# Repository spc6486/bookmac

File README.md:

# BookMac Replicas

Functional replicas of the BookMac and BookMac Mini, the 1985 tablet concepts Hartmut Esslinger (frog design) created for Apple. Esslinger's own *Keep It Simple* calls them the MacBook and MacBook Mini. Each unit is built around a Raspberry Pi 5 with a 9.7" 2048×1536 touchscreen, an internal mechanical keyboard, a battery-backed power system and period-style rear ports. Their main use is classic Mac OS (7.5.5) under SheepShaver, but they are general-purpose Pi 5 computers and run other operating systems and emulators, including Basilisk II.

There are two units, one per concept: the full-size **BookMac** and the smaller **BookMac Mini**. They share most of the hardware and all of the software; the differences are listed in `docs/` and `decals/README.md`.

The full-size concept has a floppy drive slot. This build closes it with a printed cover (`enclosure/bookmac/floppy-slot-cover.stl`), because the space behind it holds the batteries, rear ports and speakers. The Mini concept shows no floppy provision.

Both concepts are documented in Paul Kunkel, *AppleDesign* (Graphis, 1997), and Hartmut Esslinger, *Keep It Simple* (Arnoldsche, 2013). The build was inspired by Kevin Noki's functional replicas.

> **Work in progress.** This repository documents a personal build as it evolves. Expect inaccuracies, undocumented changes, and parts of the documentation that lag behind the hardware. Verify dimensions, pinouts and part numbers against your own parts before building, and please open an issue when you find an error.

> **Hobbyist designs, reference only.** The PCBs, wiring and enclosure were designed by a hobbyist, not a professional electrical or mechanical engineer. They have not been independently reviewed for electrical safety, battery safety, thermal performance or regulatory compliance. Use them as a reference for your own work, at your own risk. This is especially important for anything involving the lithium battery packs or the UPS.

> **Not affiliated with, sponsored by, or endorsed by Apple Inc.** Apple and Macintosh are trademarks of Apple Inc., used here only to identify the original concept this replica is based on. This repository contains no Apple logos or artwork.

---

## Repository contents

| Folder | Contents |
|---|---|
| `pcb/keyboard/` | 58-key matrix PCB (Cherry MX Low Profile footprint, 5 × 14): `.sch`, `.brd`, BOM, CPL |
| `pcb/keyboard-controller/` | ATmega32U4 USB-C keyboard controller: `.sch`, `.brd`, BOM, CPL |
| `pcb/rear-port-adb/` | ATmega32U4 ADB-to-USB converter (TMK) with Mini-DIN 4: `.sch`, `.brd`, BOM, CPL |
| `pcb/rear-port-power/` | Rear power and reset switch board: `.sch`, `.brd`, BOM, CPL |
| `pcb/rear-port-av/` | Composite RCA, 3.5 mm headphone pass-through, Mini-DIN 8: `.brd`, BOM, CPL |
| `firmware/keyboard/` | QMK keyboard definition, keymap and pre-built image for the internal keyboard |
| `firmware/adb/` | Pre-built TMK `adb_usb` unimap image for the ADB converter, with a link to the source |
| `enclosure/bookmac/` | Full-size STEP model and STLs, one file per part |
| `enclosure/bookmac-mini/` | Mini STEP model and STLs, one file per part |
| `enclosure/jigs/` | Keycap holder and keycap decal holder |
| `decals/` | Keycap legend decals for both units, 1:1 exports of the original artwork (SVG with outlined text, and PDF), and a README listing the differences |
| `docs/` | Components list and wiring, Pi 5 pinout, PiPower 5 installation, reference photos (`docs/images/`) |

Board files are EAGLE 9.7 format, exported from Autodesk Fusion Electronics.

Gerber packages for each board revision are attached to the GitHub Releases rather than committed.

## Related software

The Pi-side software lives in separate repositories:

| Repository | Purpose |
|---|---|
| [emulator-manager](https://github.com/spc6486/emulator-manager) | Tray launcher for SheepShaver / Basilisk II; touch shim, display geometry |
| [battery-monitor](https://github.com/spc6486/battery-monitor) | PiPower 5 (I2C) battery monitoring and safe shutdown |
| [emu-serial-bridge](https://github.com/spc6486/emu-serial-bridge) | Serial bridge between the emulated Mac and Pi-side handlers (battery, brightness, volume) |
| [emu-control-strip](https://github.com/spc6486/emu-control-strip) | Native Mac OS 7.5 Control Strip modules, Brightness control panel, Power Manager extension |
| [emu-homecontrol](https://github.com/spc6486/emu-homecontrol) | Classic Mac OS Home Assistant client |
| [brightness-control](https://github.com/spc6486/brightness-control) | Backlight brightness via Pi 5 hardware PWM |
| [volume-control](https://github.com/spc6486/volume-control) | Volume, mute and GPIO headphone/speaker toggle |
| [display-calibrator](https://github.com/spc6486/display-calibrator) | Display borders and touchscreen calibration for custom bezels |
| [kiosk-manager](https://github.com/spc6486/kiosk-manager) | Kiosk mode, boot splash and startup sound |

## Hardware overview

| Area | Parts |
|---|---|
| Compute | Raspberry Pi 5 |
| Display | 9.7" iPad Retina LCD, LTL097QL01-A01 (2048 × 1536), in both units. Full-size: VSDISPLAY VS-RTD2556HC-V2 controller. Mini: PCB800869. Each controller comes with a TLT-iPAD3 eDP adapter. |
| Touch | SingWon capacitive overlay, USB |
| Backlight | Controller's PWM output separated from the backlight DIM line, which is then driven from Pi GPIO12 (hardware PWM). See [display controller modifications](docs/components-and-wiring.md#4-display-controller-modifications). |
| Audio | Display controller's amplifier and speakers; GPIO24 switches speaker / headphones through the jack-detect line (same section) |
| Power | SunFounder PiPower 5 UPS, two 3.7 V LiPo packs in 2S, 12 V barrel input. Observed runtime is about 3–6 h. |
| Keyboard | Custom 58-key PCB, Cherry MX Low Profile switches, Gateron low-profile plate-mount stabilizers, QMK controller |
| Rear ports | 12 V DC, ADB, headphone, composite (RCA), Mini-DIN 8 |

A full components list with wiring is in `docs/`.

## Photos and reference images

<table>
<tr><td width="50%" valign="top"><br><sub>Finished BookMac Mini</sub></td><td width="50%" valign="top"><br><sub>Painted full-size case</sub></td></tr>
<tr><td width="50%" valign="top"><br><sub>Rendering of the full-size internal layout</sub></td><td width="50%" valign="top"><br><sub>Full-size internal layout, current wiring</sub></td></tr>
<tr><td width="50%" valign="top"><br><sub>Back of the full-size screen assembly: panel, speakers, display wiring</sub></td><td width="50%" valign="top"><br><sub>BookMac Mini internal layout</sub></td></tr>
<tr><td width="50%" valign="top"><br><sub>Rendering of the BookMac Mini</sub></td><td width="50%" valign="top"><br><sub>Rendering of the BookMac Mini internal layout</sub></td></tr>
</table>

The photos show the finished replica, including the Apple-style markings that are part of the concept's appearance. They are for reference; the repository does not distribute logo artwork.

## Finishing

These are the materials used on the original enclosures. Treat them as one working example, not a requirement:

- Both units printed in ASA
- Bondo glazing putty for layer lines and small defects
- SprayMAX 1K Plastic Adhesion Promoter (article 3680009)
- SprayMAX 1K white high-build primer (article 3680403), sanded after priming
- SprayMAX 1K FillClean base coat, custom-mix can (article 3682071), filled to a RAL color:
  - **BookMac (full size):** RAL 7044, as a Platinum gray match
  - **BookMac Mini:** RAL 1013, as a Snow White match

  RAL 1013 on both units would be the period-correct choice for the 1985 concepts.
- SprayMAX 2K clear coat, satin (article 3680067)
- Experts Choice decals, item 123 (artwork in `decals/`)
- Microscale MicroSet and MicroSol to help the decals conform to the concave keycaps

General practice and precautions:

- **Read the technical and safety data sheets** for every product, and follow their flash times, recoat windows and temperature and humidity ranges. They differ between products and brands.
- **2K clears typically contain isocyanates.** Use a properly fitted respirator rated for the product per its SDS, gloves and eye protection, and good ventilation. Keep other people and pets away from the spray area.
- **Work in thin coats.** Fill layer lines with thin passes of putty, then use high-build primer to bring the surface level. Sand the primer progressively finer before the base coat. Heavy single coats sag and trap solvent.
- **Test on scrap first.** That includes adhesion promoter on your filament, solvent compatibility of primer and paint with the printed part, and clear coat over a sample decal. Some solvent clears attack decals unless the first coats are light mists.
- **Decal setting solutions** soften the decal film. Apply sparingly and let them work before touching the decal; check the manufacturer's instructions for order of use.
- **Keep mating surfaces thin.** Avoid building up primer and paint on surfaces where parts join, such as bezel seats, lips and screw bosses. Excess film thickness makes parts fit poorly. Mask them, or keep coats there light.
- **Allow full cure** before assembly and handling. Fasteners and heat-set inserts can mar paint that has not fully cured.

## Building

Start with [`docs/components-and-wiring.md`](docs/components-and-wiring.md). In particular:

- **Rear power switch:** fit the momentary ALPS SPPJ223200 in place of the latching SPPJ222200 shown in the schematic. The PiPower 5 needs a momentary button.
- **Battery packs:** balance the two packs to within 50 mV of each other before wiring them in series.
- **Display controller:** backlight dimming and speaker/headphone switching need two modifications to the display controller, and both can damage it if done carelessly. Locate and test each point before soldering.
- **Keyboard ribbon:** pins 1–20 must match end to end, from the keyboard PCB's solder holes to the controller's IDC header. Check with a meter before powering up.

Fasteners are M3 and M2 pan-head screws into knurled heat-set inserts, plus M2.5 brass standoffs for the PiPower 5. The Pi 5 stacks on top of the PiPower 5.

The keyboard firmware is built with QMK; see `firmware/keyboard/README.md`. The ADB converter uses TMK's [`converter/adb_usb`](https://github.com/tmk/tmk_keyboard/tree/master/converter/adb_usb).

## Licenses

| Part | License |
|---|---|
| Enclosure (STEP/STL), PCB design files, BOMs, decals, documentation | [CC BY-NC-SA 4.0](https://creativecommons.org/licenses/by-nc-sa/4.0/) (`LICENSE`), with the additional permission below |
| Keyboard firmware (QMK) and ADB firmware (TMK) | GPL-2.0-or-later, as inherited from QMK and TMK (`firmware/LICENSE`) |
| Pi-side software (linked repositories) | MIT, except emu-control-strip (see that repository) |

The hardware is shared for others to build, modify and enjoy, not for commercial use. ShareAlike means that if you publish a modified version, it must use the same license, so improvements stay available to everyone. Because of the non-commercial term this is not "open source hardware" in the OSHWA sense.

**Additional permission: making parts at cost.** In addition to CC BY-NC-SA 4.0, you may make and supply parts, boards or kits from this repository's hardware files **at cost**. "At cost" means the price covers only materials, fabrication, shipping and payment-processing fees: no profit and no charge for labour. Group buys on these terms are allowed. Selling for profit, charging for labour, or listing on marketplaces such as Etsy or eBay requires written permission from the maintainer (GitHub user spc6486); please open an issue to ask.

Contributions are welcome. See [CONTRIBUTING.md](CONTRIBUTING.md) for the terms that apply to them.

Both enclosures are also on Thingiverse: full-size BookMac [thing:7426168](https://www.thingiverse.com/thing:7426168), BookMac Mini [thing:7427053](https://www.thingiverse.com/thing:7427053).

## Not included

- Mac OS system software or Macintosh ROM images. Obtain these yourself.
- Apple logo artwork, the case label, or other Apple decal artwork. (Photos and renders show the finished replica with its markings; no logo artwork files are included.)

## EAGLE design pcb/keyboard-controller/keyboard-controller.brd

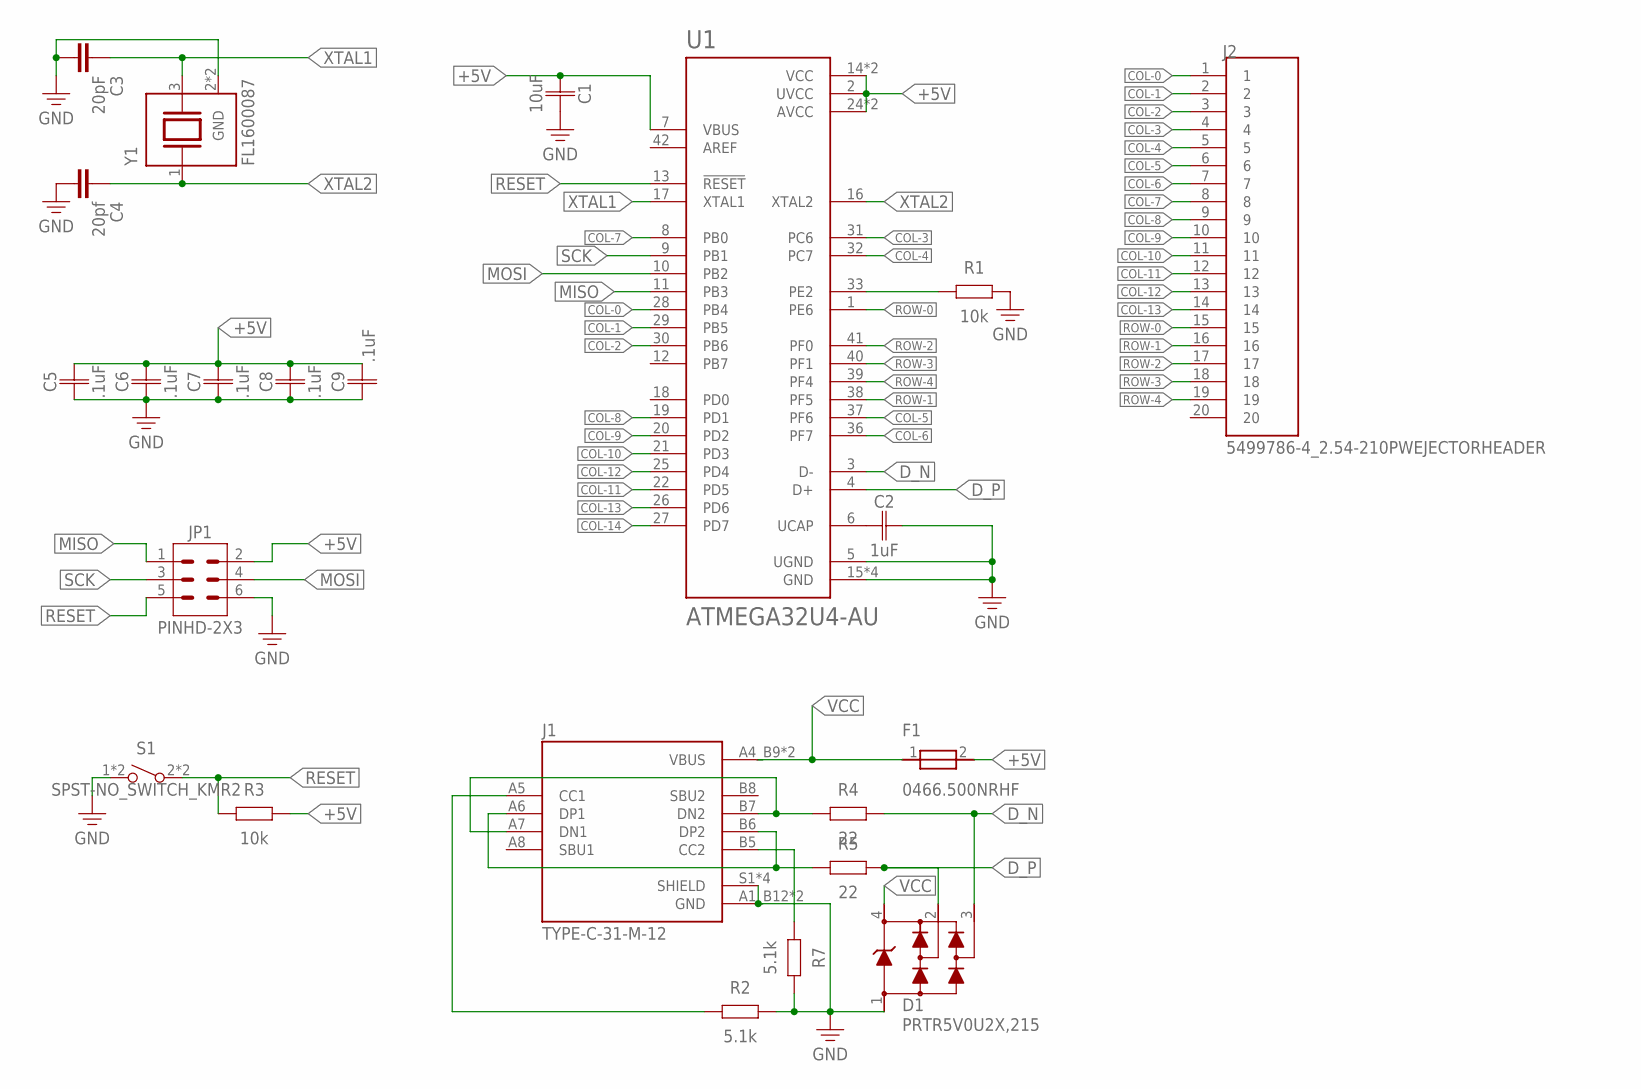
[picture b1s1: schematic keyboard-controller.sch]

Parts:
C1: 10uF; CAPC1005X60
C2: 1uF; CAPC1005X60
C3: 20pF; CAPC1005X60
C4: 20pf; CAPC1005X60
C5, C6, C7, C8, C9: .1uF; CAPC1005X60
D1: PRTR5V0U2X,215; SOT143B
F1: 0466.500NRHF; FUSC3115X66N
J1: TYPE-C-31-M-12; HRO_TYPE-C-31-M-12
J2: 5499786-4_2.54-210PWEJECTORHEADER; TE_5499786-4
JP1: PINHD-2X3; 2X03
R1, R3: 10k; RESC1005X40
R2, R7: 5.1k; RESC1005X40
R4, R5: 22; RESC1005X40
S1: SPST-NO_SWITCH_KMR2; KMR2
U1: ATMEGA32U4-AU; QFP80P1200X1200X120-44N
Y1: FL1600087; XTAL_FL1600087

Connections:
+5V: C1.1, C5.2, C6.2, C7.2, C8.2, C9.2, F1.2, JP1.2, R3.2, U1.2 (UVCC), U1.7 (VBUS), U1.14 (VCC), U1.24 (AVCC), U1.34 (VCC), U1.44 (AVCC)
CC1: J1.A5 (CC1), R2.1
CC2: J1.B5 (CC2), R7.1
COL-0: J2.1, U1.28 (PB4)
COL-1: J2.2, U1.29 (PB5)
COL-2: J2.3, U1.30 (PB6)
COL-3: J2.4, U1.31 (PC6)
COL-4: J2.5, U1.32 (PC7)
COL-5: J2.6, U1.37 (PF6)
COL-6: J2.7, U1.36 (PF7)
COL-7: J2.8, U1.8 (PB0)
COL-8: J2.9, U1.19 (PD1)
COL-9: J2.10, U1.20 (PD2)
COL-10: J2.11, U1.21 (PD3)
COL-11: J2.12, U1.22 (PD5)
COL-12: J2.13, U1.25 (PD4)
COL-13: J2.14, U1.26 (PD6)
COL-14: U1.27 (PD7)
D_N: D1.3, R4.2, U1.3 (D-)
D_P: D1.2, R5.2, U1.4 (D+)
GND: C1.2, C2.2, C3.2, C4.2, C5.1, C6.1, C7.1, C8.1, C9.1, D1.1, J1.A1_B12 (GND), J1.B1_A12 (GND), J1.S1 (SHIELD), J1.S2 (SHIELD), J1.S3 (SHIELD), J1.S4 (SHIELD), JP1.6, R1.2, R2.2, R7.2, S1.1, S1.4 (1), U1.5 (UGND), U1.15 (GND), U1.23 (GND), U1.35 (GND), U1.43 (GND), Y1.2 (GND), Y1.4 (GND)
MISO: JP1.1, U1.11 (PB3)
MOSI: JP1.4, U1.10 (PB2)
unnamed: R1.1, U1.33 (PE2)
unnamed: C2.1, U1.6 (UCAP)
unnamed: J1.A6 (DP1), J1.B6 (DP2), R5.1
unnamed: J1.A7 (DN1), J1.B7 (DN2), R4.1
RESET: JP1.5, R3.1, S1.2, S1.3 (2), U1.13 (!RESET)
ROW-0: J2.15, U1.1 (PE6)
ROW-1: J2.16, U1.38 (PF5)
ROW-2: J2.17, U1.41 (PF0)
ROW-3: J2.18, U1.40 (PF1)
ROW-4: J2.19, U1.39 (PF4)
SCK: JP1.3, U1.9 (PB1)
VCC: D1.4, F1.1, J1.A4_B9 (VBUS), J1.B4_A9 (VBUS)
XTAL1: C3.1, U1.17 (XTAL1), Y1.3 (2)
XTAL2: C4.1, U1.16 (XTAL2), Y1.1

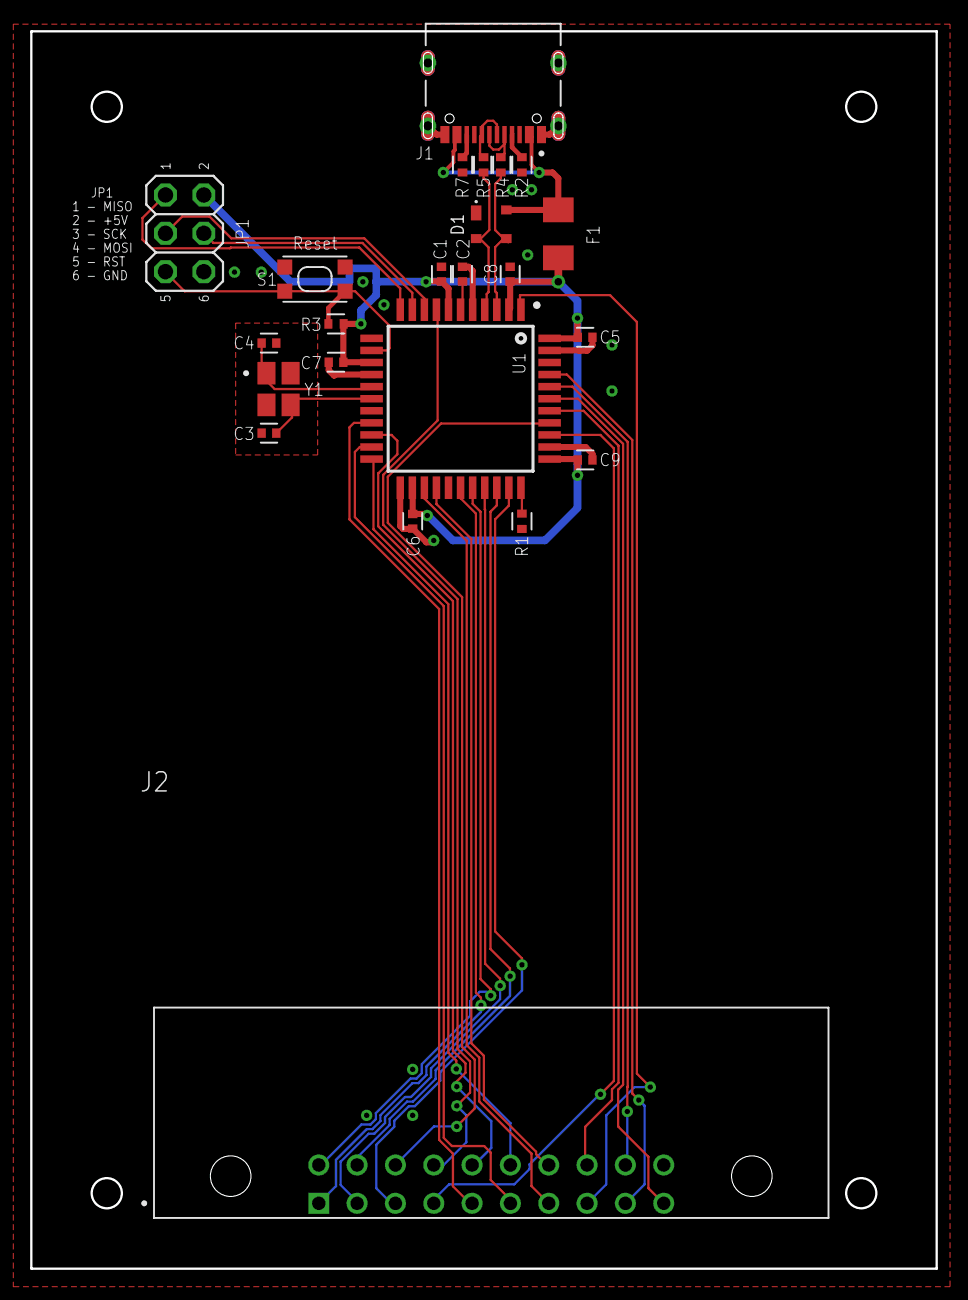
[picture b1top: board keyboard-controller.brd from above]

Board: 2 copper layers, 60.0 x 82.0 mm, 23 parts (0 on the bottom side), 36 nets.

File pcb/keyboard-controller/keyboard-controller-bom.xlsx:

Comment | Designator | Footprint | JLCPCB Part #（optional）
.1uF | C5, C6, C7, C8, C9 | CAPC1005X60
0466.500NRHF | F1 | FUSC3115X66N
10k | R1, R3 | RESC1005X40
10uF | C1 | CAPC1005X60
1uF | C2 | CAPC1005X60
20pF | C3 | CAPC1005X60
20pf | C4 | CAPC1005X60
22 | R4, R5 | RESC1005X40
5.1k | R2, R7 | RESC1005X40
5499786-4_2.54-210PWEJECTORHEADER | J2 | ORHEADER TE_5499786-4
ATMEGA32U4-AU | U1 | QFP80P1200X1200X120-44N
FL1600087 | Y1 | XTAL_FL1600087
PINHD-2X3 | JP1 | 2X03
PRTR5V0U2X,215 | D1 | SOT143B
SPST-NO_SWITCH_KMR2 | S1 | KMR2
TYPE-C-31-M-12 | J1 | HRO_TYPE-C-31-M-12

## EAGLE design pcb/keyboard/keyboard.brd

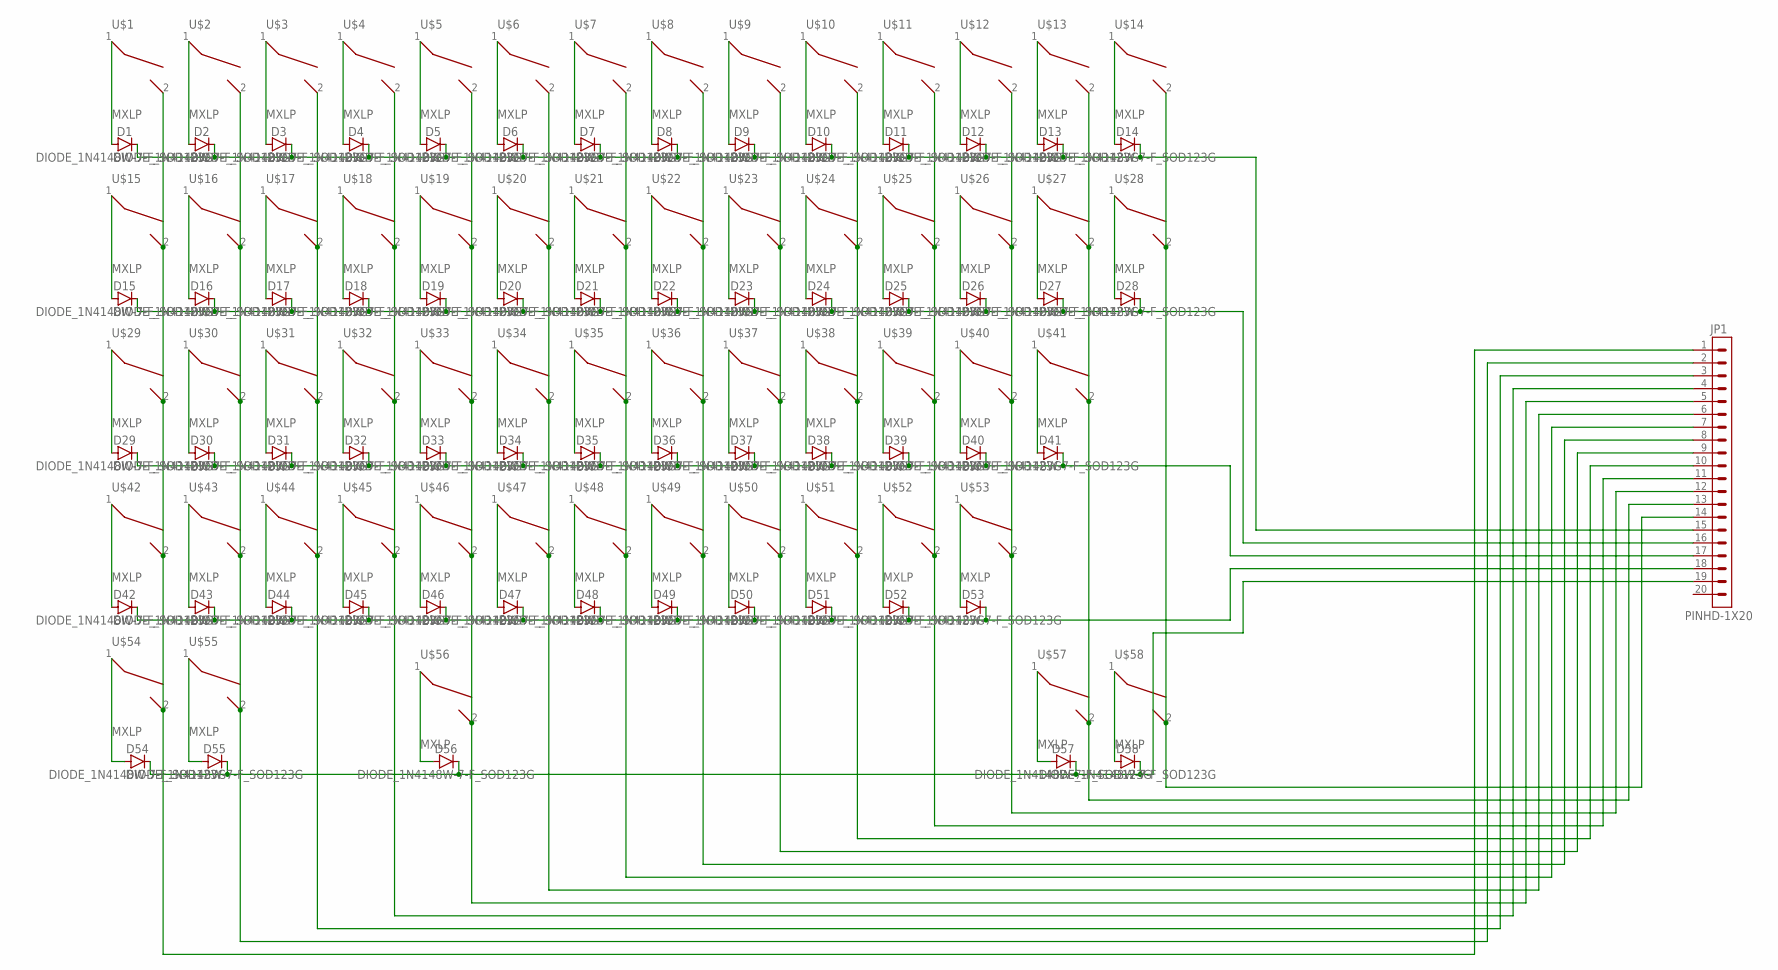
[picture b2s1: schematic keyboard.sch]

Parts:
D1, D2, D3, D4, D5, D6, D7, D8, D9, D10, D11, D12, D13, D14, D15, D16, D17, D18, D19, D20, D21, D22, D23, D24, D25, D26, D27, D28, D29, D30, D31, D32, D33, D34, D35, D36, D37, D38, D39, D40, D41, D42, D43, D44, D45, D46, D47, D48, D49, D50, D51, D52, D53, D54, D55, D56, D57, D58: DIODE_1N4148W-7-F_SOD123G; SOD3715X135
JP1: PINHD-1X20; 1X20
U$1, U$2, U$3, U$4, U$5, U$6, U$7, U$8, U$9, U$10, U$11, U$12, U$13, U$14, U$15, U$16, U$17, U$18, U$19, U$20, U$21, U$22, U$23, U$24, U$25, U$26, U$27, U$28, U$29, U$30, U$31, U$32, U$33, U$34, U$35, U$36, U$37, U$38, U$39, U$40, U$41, U$42, U$43, U$44, U$45, U$46, U$47, U$48, U$49, U$50, U$51, U$52, U$53, U$54, U$55, U$56, U$57, U$58: MXLP; CHERRY-MX-LOW-PROFILE

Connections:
unnamed: D1.2 (A), U$1.1
unnamed: D2.2 (A), U$2.1
unnamed: JP1.3, U$3.2, U$17.2, U$31.2, U$44.2
unnamed: D3.2 (A), U$3.1
unnamed: D4.2 (A), U$4.1
unnamed: D5.2 (A), U$5.1
unnamed: D6.2 (A), U$6.1
unnamed: D7.2 (A), U$7.1
unnamed: D8.2 (A), U$8.1
unnamed: D9.2 (A), U$9.1
unnamed: D10.2 (A), U$10.1
unnamed: D11.2 (A), U$11.1
unnamed: D12.2 (A), U$12.1
unnamed: D13.2 (A), U$13.1
unnamed: D14.2 (A), U$14.1
unnamed: D15.2 (A), U$15.1
unnamed: D16.2 (A), U$16.1
unnamed: D17.2 (A), U$17.1
unnamed: D18.2 (A), U$18.1
unnamed: D19.2 (A), U$19.1
unnamed: D20.2 (A), U$20.1
unnamed: D21.2 (A), U$21.1
unnamed: D22.2 (A), U$22.1
unnamed: D23.2 (A), U$23.1
unnamed: D24.2 (A), U$24.1
unnamed: D25.2 (A), U$25.1
unnamed: D26.2 (A), U$26.1
unnamed: D27.2 (A), U$27.1
unnamed: D28.2 (A), U$28.1
unnamed: D15.1 (C), D16.1 (C), D17.1 (C), D18.1 (C), D19.1 (C), D20.1 (C), D21.1 (C), D22.1 (C), D23.1 (C), D24.1 (C), D25.1 (C), D26.1 (C), D27.1 (C), D28.1 (C), JP1.16
unnamed: D29.2 (A), U$29.1
unnamed: D30.2 (A), U$30.1
unnamed: D31.2 (A), U$31.1
unnamed: D32.2 (A), U$32.1
unnamed: D33.2 (A), U$33.1
unnamed: D34.2 (A), U$34.1
unnamed: D35.2 (A), U$35.1
unnamed: D36.2 (A), U$36.1
unnamed: D37.2 (A), U$37.1
unnamed: D38.2 (A), U$38.1
unnamed: D39.2 (A), U$39.1
unnamed: D40.2 (A), U$40.1
unnamed: D41.2 (A), U$41.1
unnamed: D29.1 (C), D30.1 (C), D31.1 (C), D32.1 (C), D33.1 (C), D34.1 (C), D35.1 (C), D36.1 (C), D37.1 (C), D38.1 (C), D39.1 (C), D40.1 (C), D41.1 (C), JP1.17
unnamed: D42.2 (A), U$42.1
unnamed: D43.2 (A), U$43.1
unnamed: D44.2 (A), U$44.1
unnamed: D45.2 (A), U$45.1
unnamed: D46.2 (A), U$46.1
unnamed: D47.2 (A), U$47.1
unnamed: D48.2 (A), U$48.1
unnamed: D49.2 (A), U$49.1
unnamed: D50.2 (A), U$50.1
unnamed: D51.2 (A), U$51.1
unnamed: D52.2 (A), U$52.1
unnamed: D53.2 (A), U$53.1
unnamed: D42.1 (C), D43.1 (C), D44.1 (C), D45.1 (C), D46.1 (C), D47.1 (C), D48.1 (C), D49.1 (C), D50.1 (C), D51.1 (C), D52.1 (C), D53.1 (C), JP1.18
unnamed: D54.2 (A), U$54.1
unnamed: D55.2 (A), U$55.1
unnamed: D56.2 (A), U$56.1
unnamed: D57.2 (A), U$57.1
unnamed: D58.2 (A), U$58.1
unnamed: D54.1 (C), D55.1 (C), D56.1 (C), D57.1 (C), D58.1 (C), JP1.19
unnamed: JP1.1, U$1.2, U$15.2, U$29.2, U$42.2, U$54.2
unnamed: JP1.2, U$2.2, U$16.2, U$30.2, U$43.2, U$55.2
unnamed: JP1.4, U$4.2, U$18.2, U$32.2, U$45.2
unnamed: JP1.5, U$5.2, U$19.2, U$33.2, U$46.2, U$56.2
unnamed: JP1.6, U$6.2, U$20.2, U$34.2, U$47.2
unnamed: JP1.7, U$7.2, U$21.2, U$35.2, U$48.2
unnamed: JP1.8, U$8.2, U$22.2, U$36.2, U$49.2
unnamed: JP1.9, U$9.2, U$23.2, U$37.2, U$50.2
unnamed: JP1.10, U$10.2, U$24.2, U$38.2, U$51.2
unnamed: JP1.11, U$11.2, U$25.2, U$39.2, U$52.2
unnamed: JP1.12, U$12.2, U$26.2, U$40.2, U$53.2
unnamed: JP1.13, U$13.2, U$27.2, U$41.2, U$57.2
unnamed: JP1.14, U$14.2, U$28.2, U$58.2
ROW1: D1.1 (C), D2.1 (C), D3.1 (C), D4.1 (C), D5.1 (C), D6.1 (C), D7.1 (C), D8.1 (C), D9.1 (C), D10.1 (C), D11.1 (C), D12.1 (C), D13.1 (C), D14.1 (C), JP1.15

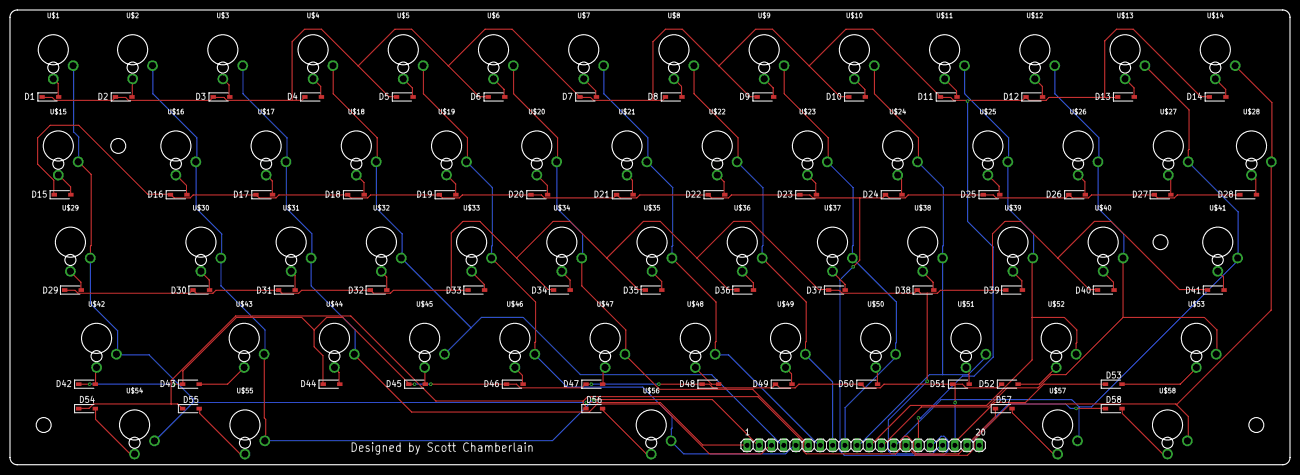
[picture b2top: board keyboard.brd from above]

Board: 2 copper layers, 266.0 x 94.5 mm, 117 parts (0 on the bottom side), 77 nets.

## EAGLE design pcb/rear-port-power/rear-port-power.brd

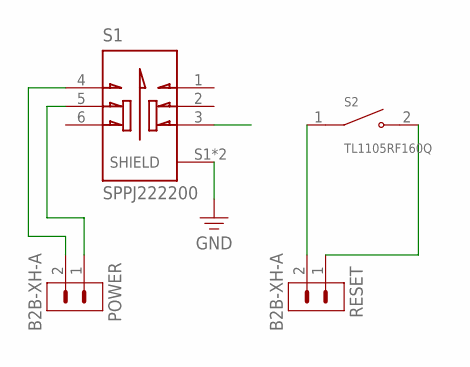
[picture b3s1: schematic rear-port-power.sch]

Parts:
POWER: B2B-XH-A
RESET: B2B-XH-A
S1: SPPJ222200; SW_SPPJ222200
S2: TL1105RF160Q; SW_TL1105RF160Q

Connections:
GND: S1.S1 (SHIELD), S1.S2 (SHIELD)
unnamed: POWER.2, S1.4
unnamed: POWER.1, S1.5
unnamed: RESET.2, S2.1
unnamed: RESET.1, S2.2

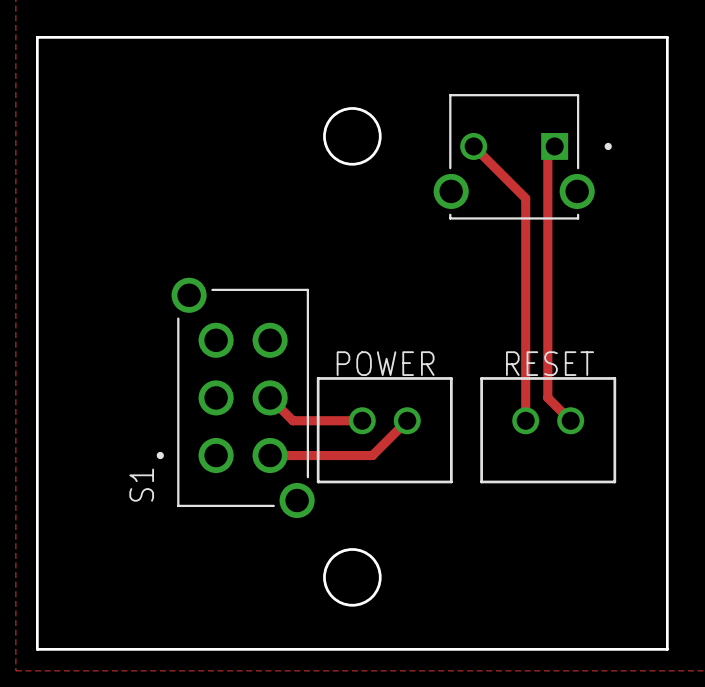
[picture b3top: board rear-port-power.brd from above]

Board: 2 copper layers, 35.0 x 34.0 mm, 4 parts (0 on the bottom side), 5 nets.

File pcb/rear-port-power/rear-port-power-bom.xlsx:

Comment | Designator | Footprint | JLCPCB Part #（optional）
B2B-XH-A | POWER,RESET | B2B-XH-A
SPPJ222200 | S1 | SW_SPPJ222200
TL1105RF160Q | S2 | SW_TL1105RF160Q

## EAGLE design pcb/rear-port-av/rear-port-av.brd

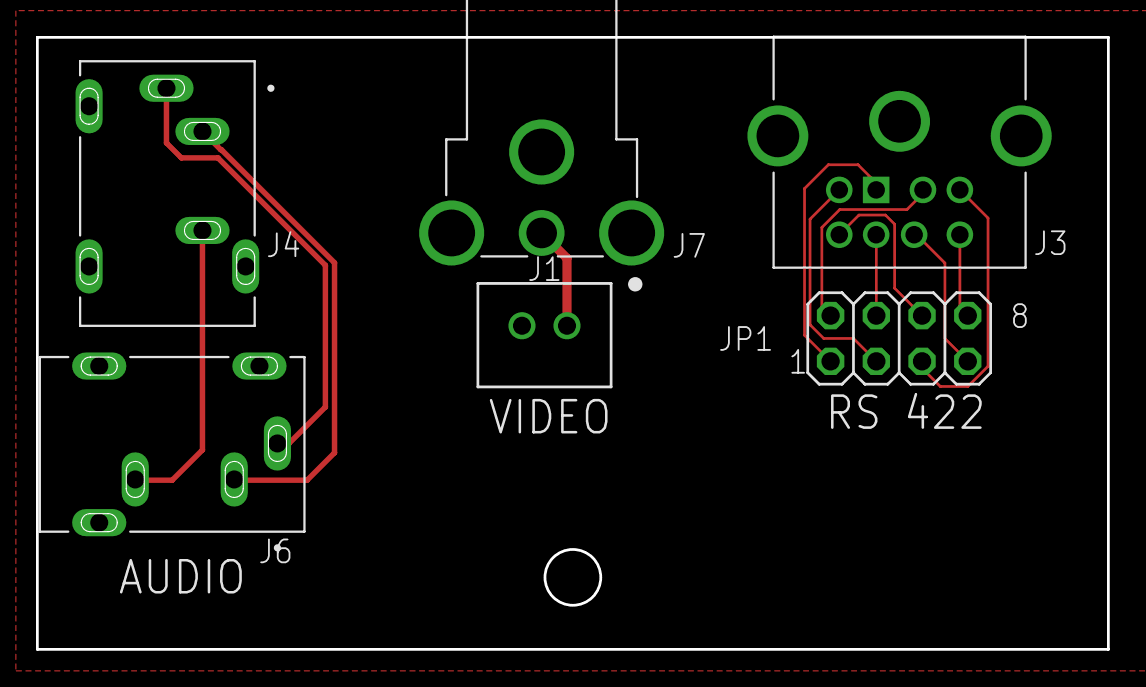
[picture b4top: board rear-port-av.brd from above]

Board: 2 copper layers, 59.5 x 34.0 mm, 6 parts (0 on the bottom side), 13 nets.

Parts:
J1: B2B-XH-A
J3: 1658998-1; TE_1658998-1
J4, J6: SJ1-3533NS; CUI_SJ1-3533NS
J7: RCJ-011; CUI_RCJ-011
JP1: PINHD-2X4; 2X04

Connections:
D1: J3.1, JP1.1
D2: J3.2, JP1.2
D3: J3.3, JP1.3
D4: J3.4, JP1.4
D5: J3.5, JP1.5
D6: J3.6, JP1.6
D7: J3.7, JP1.7
D8: J3.8, JP1.8
GND: J1.1, J3.S1, J3.S2, J3.S3, J4.SH1, J4.SH2, J4.SH3, J6.SH1, J6.SH2, J6.SH3, J7.1A, J7.1B, J7.1C
unnamed: J4.1, J6.1
unnamed: J1.2, J7.2
unnamed: J4.3, J6.3
unnamed: J4.2, J6.2

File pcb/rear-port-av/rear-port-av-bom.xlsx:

Comment | Designator | Footprint | JLCPCB Part #（optional）
1658998-1 | J3 | 1658998-1
B2B-XH-A | J1 | B2B-XH-A
PINHD-2X4 | JP1 | PINHD-2X4
RCJ-011 | J7 | RCJ-011
SJ1-3533NS | J4, J6 | SJ1-3533NS
